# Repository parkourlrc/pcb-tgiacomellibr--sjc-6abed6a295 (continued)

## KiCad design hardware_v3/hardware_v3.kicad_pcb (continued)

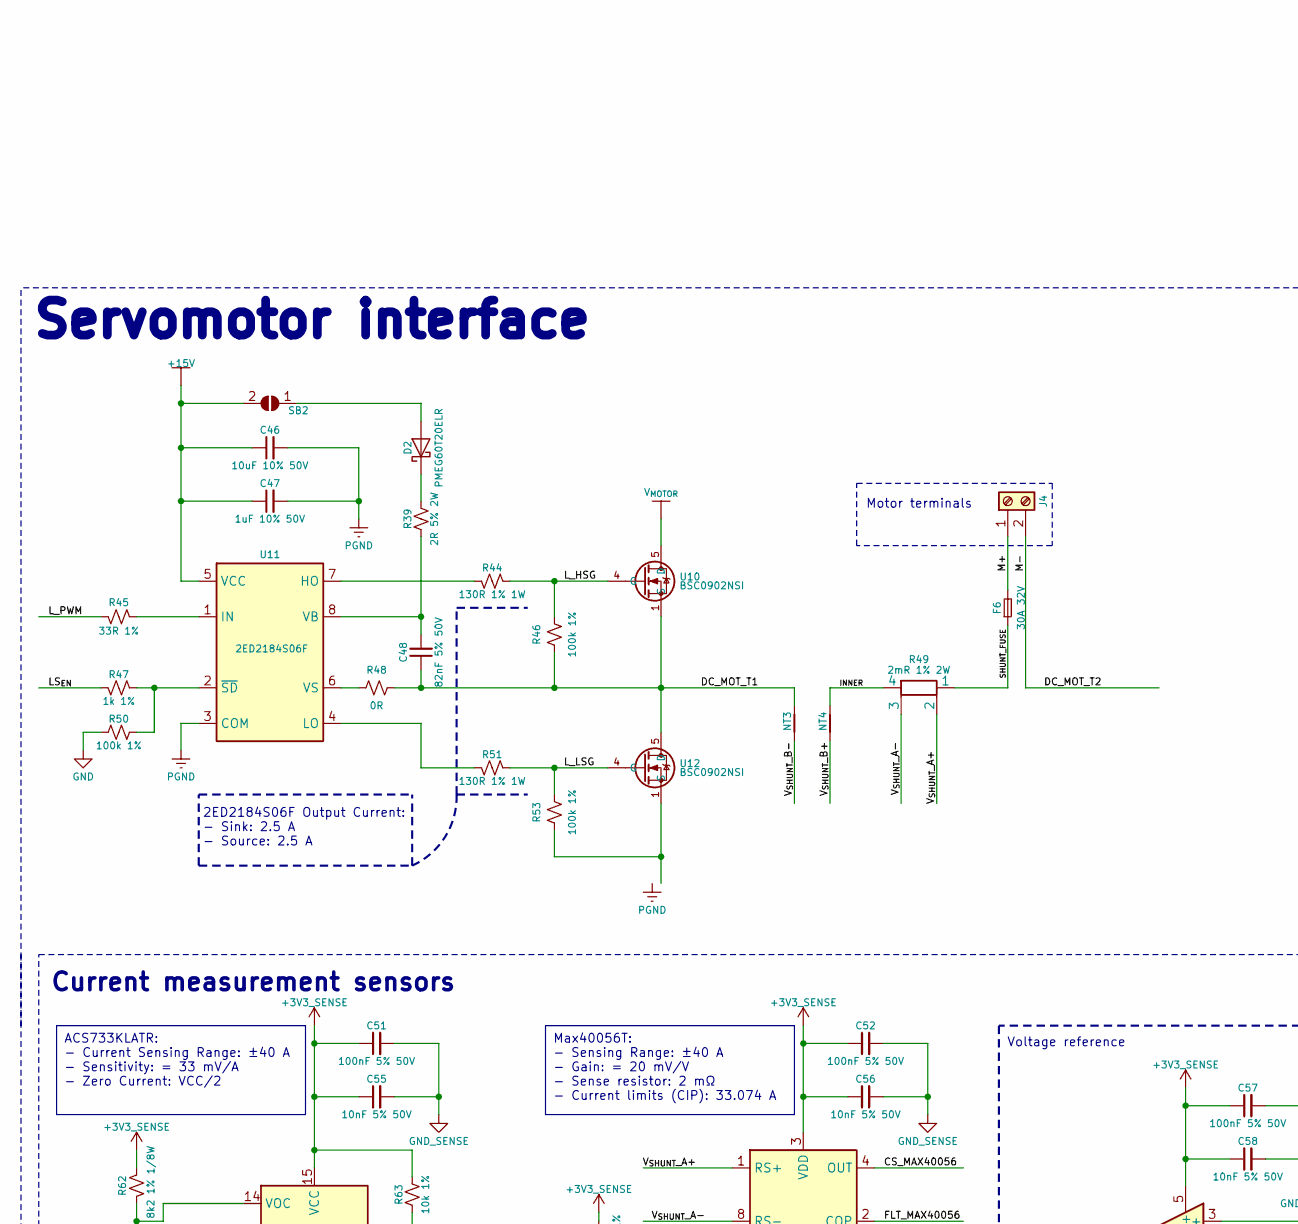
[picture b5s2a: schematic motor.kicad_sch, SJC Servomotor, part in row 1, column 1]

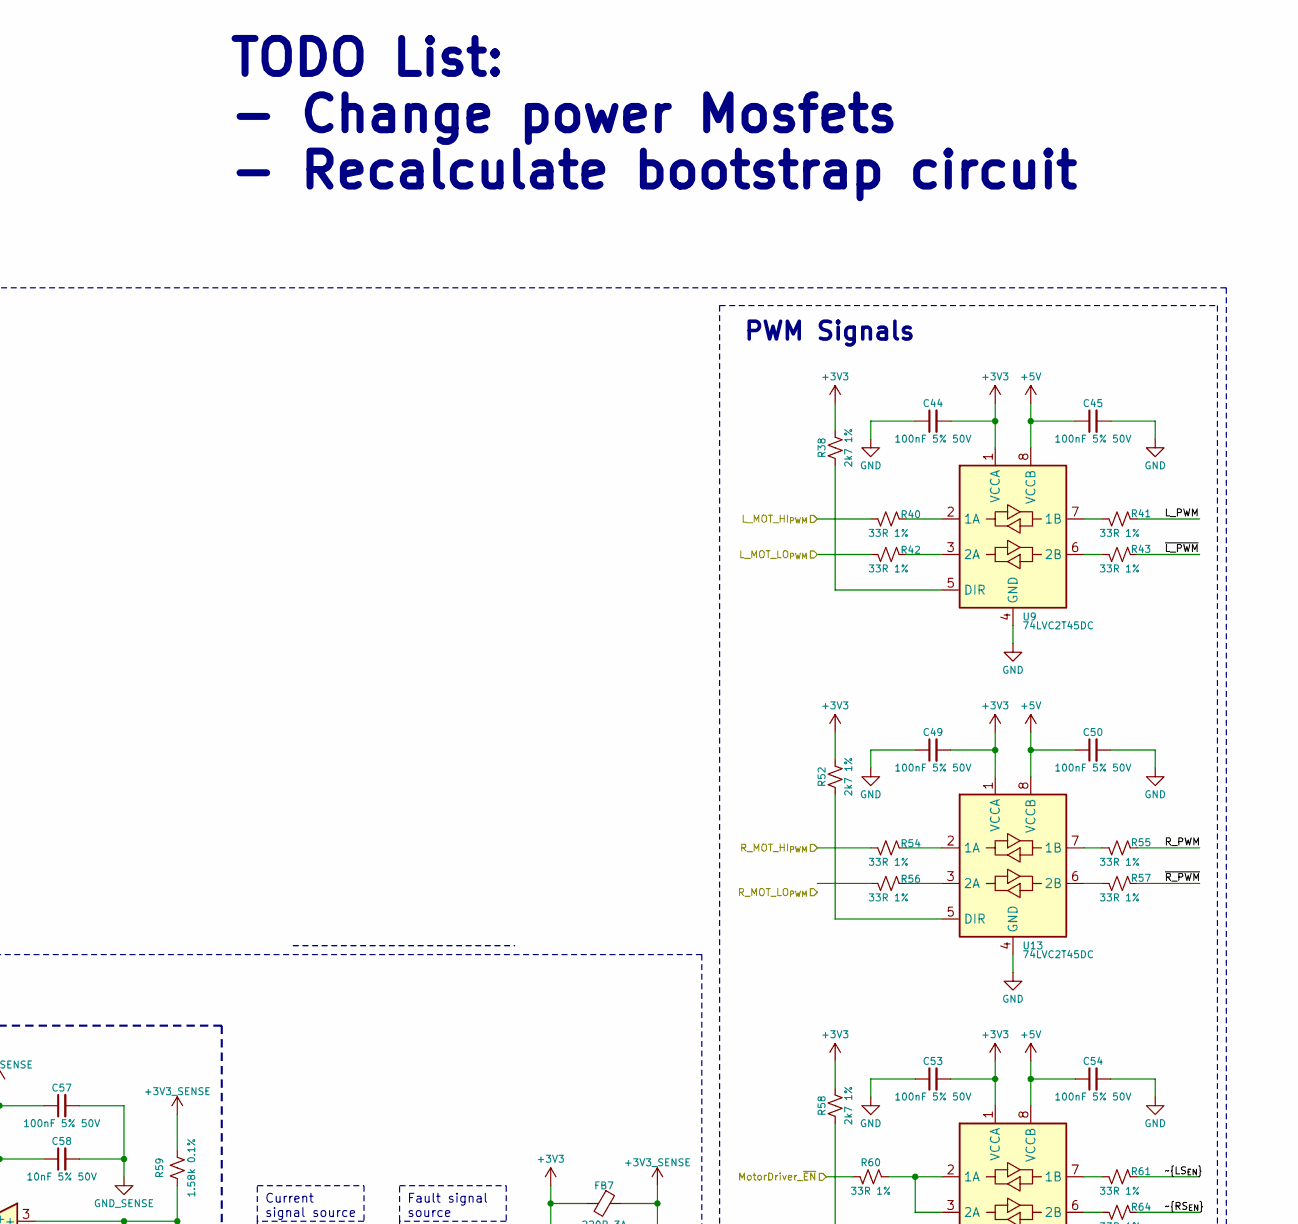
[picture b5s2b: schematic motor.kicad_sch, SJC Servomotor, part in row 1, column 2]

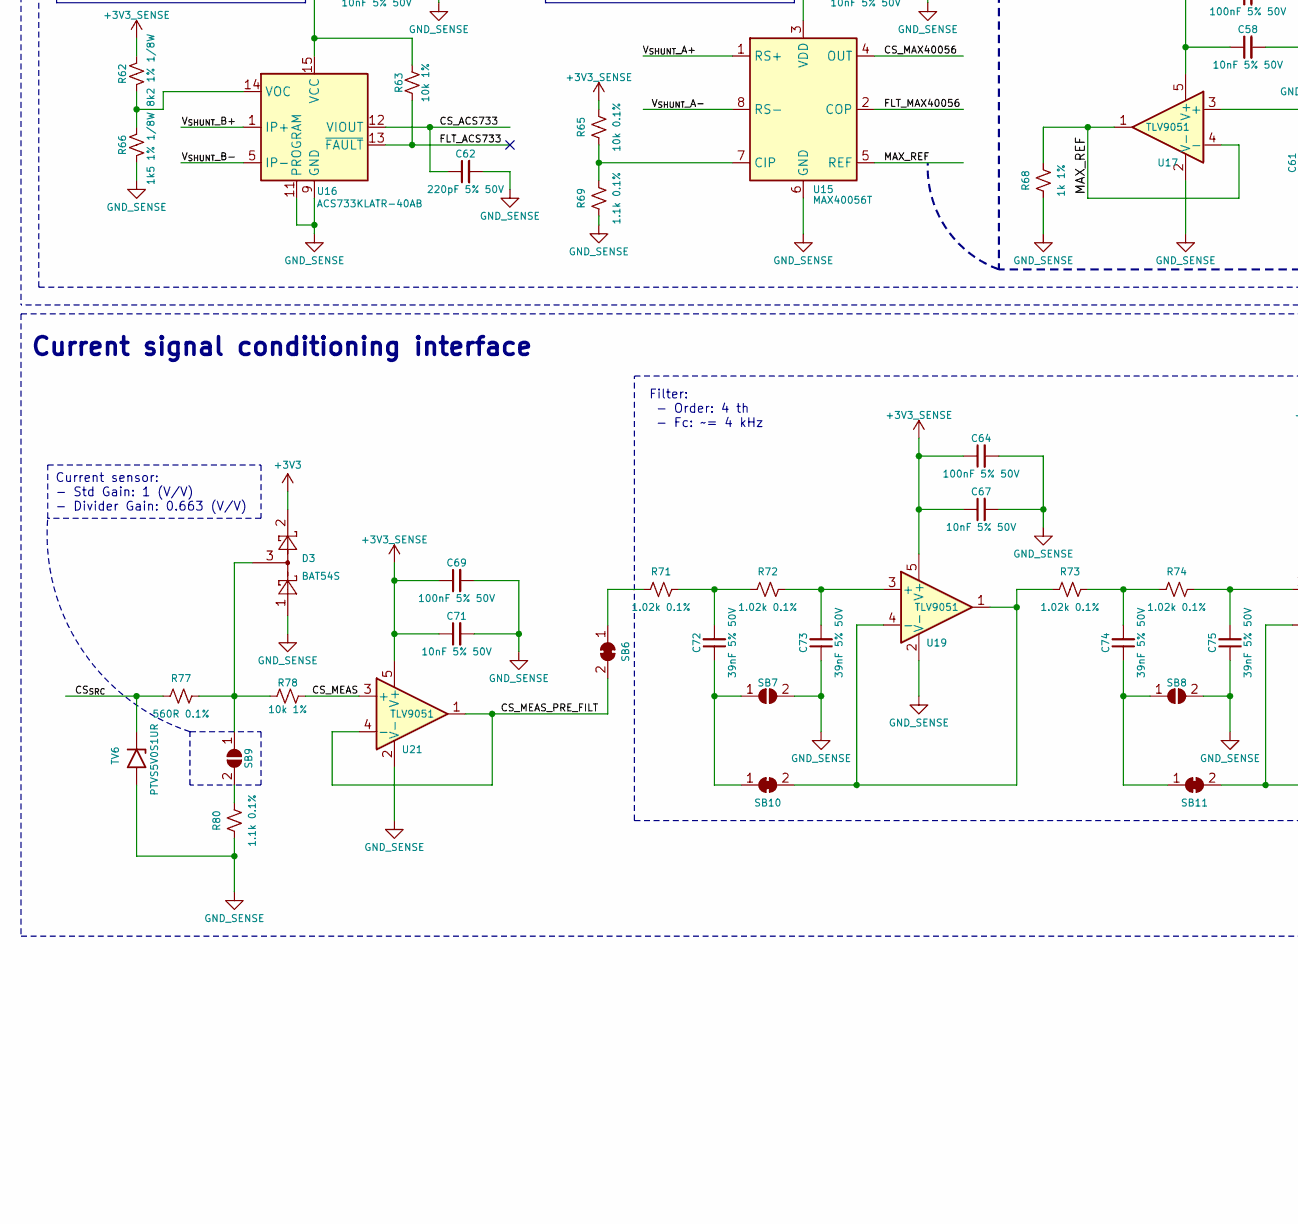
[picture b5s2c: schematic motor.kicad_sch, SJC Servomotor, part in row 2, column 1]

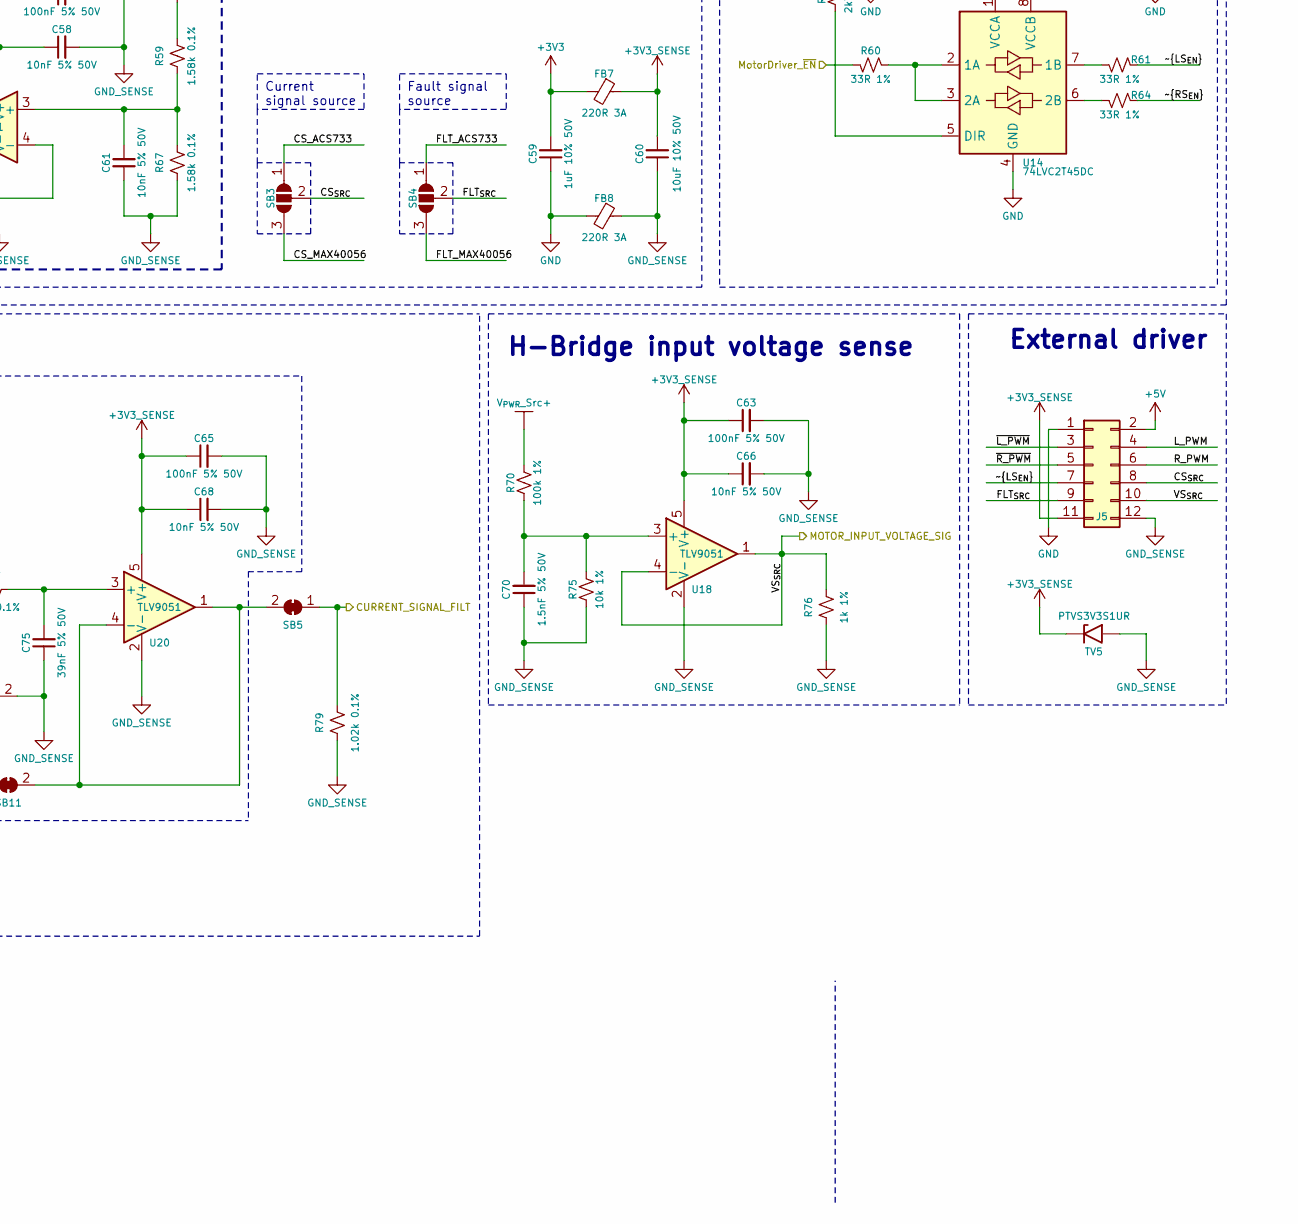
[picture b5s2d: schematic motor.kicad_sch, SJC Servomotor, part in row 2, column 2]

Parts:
C44, C45, C49, C50, C51, C52, C53, C54, C57, C63, C64, C65, C69: 100nF 5% 50V; C_0603_1608Metric; JLCPCB Part # C91183
C46, C60: 10uF 10% 50V; C_1206_3216Metric; JLCPCB Part # C13585
C47, C59: 1uF 10% 50V; C_1206_3216Metric; JLCPCB Part # C1848
C48: 82nF 5% 50V; C_0805_2012Metric_Pad1.18x1.45mm_HandSolder; JLCPCB Part # C520047
C55, C56, C58, C61, C66, C67, C68, C71: 10nF 5% 50V; C_0603_1608Metric; JLCPCB Part # C389113
C62: 220pF 5% 50V; C_0402_1005Metric_Pad0.74x0.62mm_HandSolder; JLCPCB Part # C301973
C70: 1.5nF 5% 50V; C_0603_1608Metric; JLCPCB Part # C107039
C72, C73, C74, C75: 39nF 5% 50V; C_0603_1608Metric; JLCPCB Part # C519553
D2: PMEG60T20ELR; D_SOD-123F; JLCPCB Part # C552947
D3: BAT54S; SOT-23; JLCPCB Part # C19726
F6: 30A 32V; Fuse_1206_3216Metric_Pad1.42x1.75mm_HandSolder; JLCPCB Part # C2925002
FB7, FB8: 220R 3A; L_0805_2012Metric_Pad1.05x1.20mm_HandSolder; JLCPCB Part # C76818
J4: Motor; AMASS_XT60PW-F_1x02_P7.20mm_Horizontal; JLCPCB Part # C428722
J5: Motor_Signals; PinHeader_2x06_P2.54mm_Vertical; JLCPCB Part # C225521
NT3, NT4: NetTie_2; NetTie-2_SMD_Pad2.0mm
R38, R52, R58: 2k7 1%; R_0603_1608Metric; JLCPCB Part # C114612
R39: 2R 5% 2W; R_2512_6332Metric_Pad1.40x3.35mm_HandSolder; JLCPCB Part # C91926
R40, R41, R42, R43, R45, R54, R55, R56, R57, R60, R61, R64: 33R 1%; R_0603_1608Metric; JLCPCB Part # C108661
R44, R51: 130R 1% 1W; R_2512_6332Metric_Pad1.40x3.35mm_HandSolder; JLCPCB Part # C728111
R46, R50, R53, R70: 100k 1%; R_0603_1608Metric; JLCPCB Part # C14675
R47, R68, R76: 1k 1%; R_0603_1608Metric; JLCPCB Part # C22548
R48: 0R; R_0603_1608Metric; JLCPCB Part # C103196
R49: 2mR 1% 2W; R_Shunt_2512_6332Metric_Pad1.40x3.35mm_HandSolder; JLCPCB Part # C782073
R59, R67: 1.58k 0.1%; R_0603_1608Metric; JLCPCB Part # C2441192
R62: 8k2 1% 1/8W; R_0805_2012Metric_Pad1.20x1.40mm_HandSolder; JLCPCB Part # C114545
R63, R75, R78: 10k 1%; R_0603_1608Metric; JLCPCB Part # C98220
R65: 10k 0.1%; R_0805_2012Metric_Pad1.20x1.40mm_HandSolder; JLCPCB Part # C705819
R66: 1k5 1% 1/8W; R_0805_2012Metric_Pad1.20x1.40mm_HandSolder; JLCPCB Part # C163950
R69, R80: 1.1k 0.1%; R_0603_1608Metric; JLCPCB Part # C543640
R71, R72, R73, R74, R79: 1.02k 0.1%; R_0603_1608Metric; JLCPCB Part # C705819
R77: 560R 0.1%; R_0603_1608Metric; JLCPCB Part # C351641
SB2, SB7, SB8, SB9: SolderJumper-2_P1.3mm_Open_RoundedPad1.0x1.5mm
SB3, SB4: CS_SEL; SolderJumper-3_P1.3mm_Open_RoundedPad1.0x1.5mm
SB5, SB6, SB10, SB11: SolderJumper-2_P1.3mm_Bridged2Bar_RoundedPad1.0x1.5mm
TV5: PTVS3V3S1UR; D_SOD-123; JLCPCB Part # C183521
TV6: PTVS5V0S1UR; D_SOD-123; JLCPCB Part # C478011
U9, U13, U14: 74LVC2T45DC; VSSOP-8_2.3x2mm_P0.5mm; JLCPCB Part # C730237
U10, U12: BSC0902NSI; TDSON-8-1; JLCPCB Part # C534382
U11: 2ED2184S06F; Infineon_PG-DSO-8-24_4x5mm; JLCPCB Part # C1848362
U15: MAX40056T; Texas_S-PDSO-G8_3x3mm_P0.65mm; Mouser # 700-MAX40056TAUA+
U16: ACS733KLATR-40AB; SOIC-16W_7.5x10.3mm_P1.27mm; JLCPCB Part # C459339
U17, U18, U19, U20, U21: TLV9051; SOT-23-5; JLCPCB Part # C1849429

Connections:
+3V3: C44.2, C49.2, C53.2, C59.2, D3.2, FB7.2, R38.2, R52.2, R58.2, U9.1 (VCCA), U13.1 (VCCA), U14.1 (VCCA); also elsewhere on the board
+3V3_SENSE: C51.1, C52.1, C55.1, C56.1, C57.1, C58.1, C60.2, C63.1, C64.1, C65.1, C66.1, C67.1, C68.1, C69.1, C71.1, FB7.1, J5.11, R59.2, R62.1, R63.2, R65.2, TV5.1 (K), U15.3 (VDD), U16.15 (VCC), U16.16 (VCC), U17.5 (V+), U18.5 (V+), U19.5 (V+), U20.5 (V+), U21.5 (V+)
+5V: C45.1, C50.1, C54.1, J5.2, U9.8 (VCCB), U13.8 (VCCB), U14.8 (VCCB); also elsewhere on the board
+15V: C46.1, C47.1, SB2.2 (B), U11.5 (VCC)
/Control/CURRENT_SIGNAL_FILT: R79.2, SB5.1 (A); also elsewhere on the board
/Control/L_MOT_HI_{PWM}: R40.2; also elsewhere on the board
/Control/L_MOT_LO_{PWM}: R42.2; also elsewhere on the board
/Control/MotorDriver_~EN: R60.2
/Control/R_MOT_HI_{PWM}: R54.2; also elsewhere on the board
/Motor/CS_ACS733: C62.1, SB3.1 (A), U16.12 (VIOUT)
/Motor/CS_MAX40056: SB3.3 (B), U15.4 (OUT)
/Motor/CS_MEAS: R78.2, U21.3 (+)
/Motor/CS_MEAS_PRE_FILT: SB6.2 (B), U21.1, U21.4 (-)
/Motor/CS_{SRC}: J5.8, R77.1, SB3.2 (C), TV6.1 (K)
/Motor/DC_MOT_T1: C48.1, NT3.1, R46.1, R48.2, U10.1 (S), U10.2 (S), U10.3 (S), U12.5 (D)
/Motor/DC_MOT_T2: J4.2
/Motor/FLT_ACS733: R63.1, SB4.1 (A), U16.13 (~FAULT)
/Motor/FLT_MAX40056: SB4.3 (B), U15.2 (COP)
/Motor/FLT_{SRC}: J5.9, SB4.2 (C)
/Motor/INNER: NT4.1, R49.4
/Motor/LS_{EN}: R47.2
/Motor/L_HSG: R44.1, R46.2, U10.4 (G)
/Motor/L_LSG: R51.1, R53.2, U12.4 (G)
/Motor/L_PWM: J5.4, R41.1, R45.2
/Motor/M+: F6.2, J4.1
/Motor/MAX_REF: R68.2, U15.5 (REF), U17.1, U17.4 (-)
/Motor/R_PWM: J5.6, R55.1
/Motor/SHUNT_FUSE: F6.1, R49.1
/Motor/VS_{SRC}: J5.10, R76.2, U18.1, U18.4 (-); also elsewhere on the board
/Motor/V_{SHUNT}_A+: R49.2, U15.1 (RS+)
/Motor/V_{SHUNT}_A-: R49.3, U15.8 (RS-)
/Motor/V_{SHUNT}_B+: NT4.2, U16.1 (IP+), U16.2 (IP+), U16.3 (IP+), U16.4 (IP+)
/Motor/V_{SHUNT}_B-: NT3.2, U16.5 (IP-), U16.6 (IP-), U16.7 (IP-), U16.8 (IP-)
/Motor/~LS_{EN}: J5.7, R61.1
/Motor/~L_PWM: J5.3, R43.1
/Motor/~RS_{EN}: R64.1
/Motor/~R_PWM: J5.5, R57.1
GND: C44.1, C45.2, C49.1, C50.2, C53.1, C54.2, C59.1, FB8.2, J5.1, R50.1, U9.4 (GND), U13.4 (GND), U14.4 (GND); also elsewhere on the board
GND_SENSE: C51.2, C52.2, C55.2, C56.2, C57.2, C58.2, C60.1, C61.1, C62.2, C63.2, C64.2, C65.2, C66.2, C67.2, C68.2, C69.2, C70.1, C71.2, C73.1, C75.1, D3.1, FB8.1, J5.12, R66.2, R67.1, R68.1, R69.1, R75.1, R76.1, R79.1, R80.1, SB7.2 (B), SB8.2 (B), TV5.2 (A), TV6.2 (A), U15.6 (GND), U16.9 (GND), U16.10 (GND), U16.11 (PROGRAM), U17.2 (V-), U18.2 (V-), U19.2 (V-), U20.2 (V-), U21.2 (V-)
unnamed: C72.2, R71.2, R72.1
unnamed: C74.2, R73.2, R74.1
unnamed: D2.2 (A), SB2.1 (A)
unnamed: D2.1 (K), R39.2
unnamed: R53.1, U12.1 (S), U12.2 (S), U12.3 (S)
unnamed: R71.1, SB6.1 (A)
unnamed: D3.3, R77.2, R78.1, SB9.1 (A)
unnamed: R80.2, SB9.2 (B)
unnamed: C72.1, SB7.1 (A), SB10.1 (A)
unnamed: R73.1, SB10.2 (B), U19.1, U19.4 (-)
unnamed: C74.1, SB8.1 (A), SB11.1 (A)
unnamed: SB5.2 (B), SB11.2 (B), U20.1, U20.4 (-)
unnamed: R40.1, U9.2 (1A)
unnamed: R41.2, U9.7 (1B)
unnamed: R42.1, U9.3 (2A)
unnamed: R43.2, U9.6 (2B)
unnamed: R38.1, U9.5 (DIR)
unnamed: R44.2, U11.7 (HO)
unnamed: R45.1, U11.1 (IN)
unnamed: R51.2, U11.4 (LO)
unnamed: C48.2, R39.1, U11.8 (VB)
unnamed: R48.1, U11.6 (VS)
unnamed: R47.1, R50.2, U11.2 (~SD)
unnamed: R54.1, U13.2 (1A)
unnamed: R55.2, U13.7 (1B)
unnamed: R56.1, U13.3 (2A)
unnamed: R57.2, U13.6 (2B)
unnamed: R52.1, U13.5 (DIR)
unnamed: R60.1, U14.2 (1A), U14.3 (2A)
unnamed: R61.2, U14.7 (1B)
unnamed: R64.2, U14.6 (2B)
unnamed: R58.1, U14.5 (DIR)
unnamed: R65.1, R69.2, U15.7 (CIP)
unnamed: R62.2, R66.1, U16.14 (VOC)
unnamed: C61.2, R59.1, R67.2, U17.3 (+)
unnamed: C70.2, R70.1, R75.2, U18.3 (+)
unnamed: C73.2, R72.2, U19.3 (+)
unnamed: C75.2, R74.2, U20.3 (+)
PGND: C46.2, C47.2, U11.3 (COM); also elsewhere on the board
V_{MOTOR}: U10.5 (D)
V_{PWR}_Src+: R70.2; also elsewhere on the board

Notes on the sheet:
Current sensor: - Std Gain: 1 (V/V) - Divider Gain: 0.663 (V/V)
ACS733KLATR: - Current Sensing Range: ±40 A - Sensitivity: = 33 mV/A - Zero Current: VCC/2
Fault signal source
Max40056T: - Sensing Range: ±40 A - Gain: = 20 mV/V - Sense resistor: 2 mΩ - Current limits (CIP): 33.074 A
Current signal source
Current signal conditioning interface
H-Bridge input voltage sense
Voltage reference
External driver
Filter: - Order: 4 th - Fc: ~= 4 kHz
2ED2184S06F Output Current: - Sink: 2.5 A - Source: 2.5 A
Servomotor interface
Motor terminals
PWM Signals
Current measurement sensors
TODO List: - Change power Mosfets - Recalculate bootstrap circuit

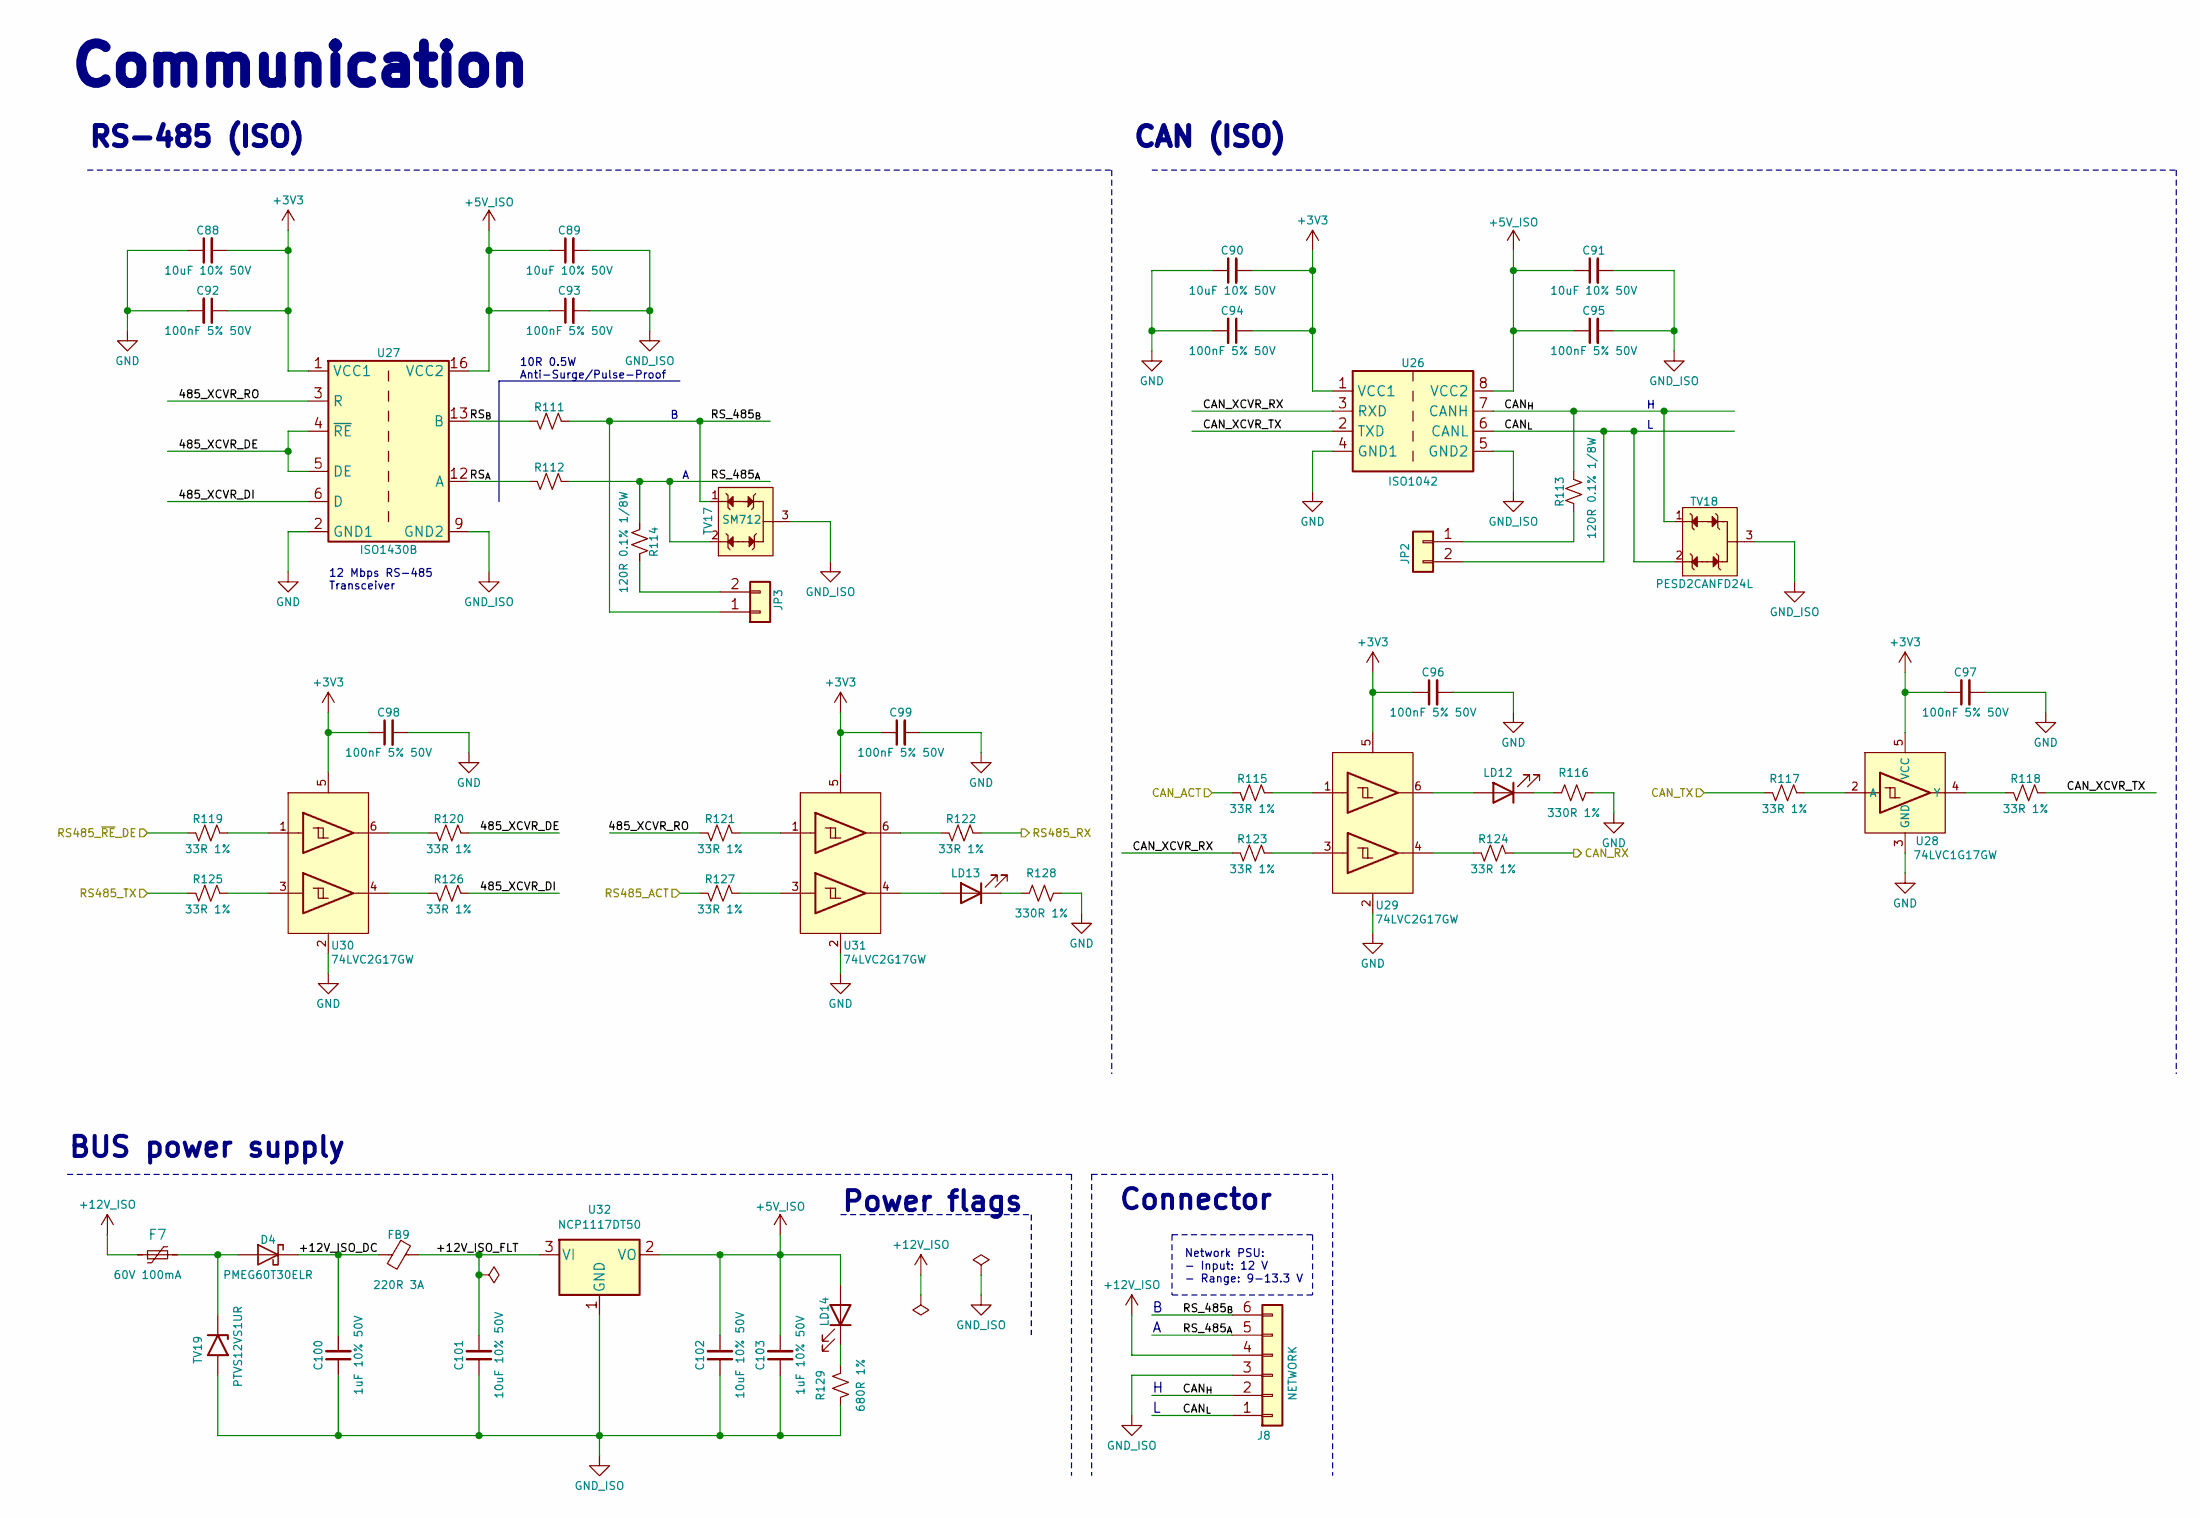
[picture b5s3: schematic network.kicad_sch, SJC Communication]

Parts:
C88, C89, C90, C91, C101, C102: 10uF 10% 50V; C_1206_3216Metric; JLCPCB Part # C13585
C92, C93, C94, C95, C96, C97, C98, C99: 100nF 5% 50V; C_0603_1608Metric; JLCPCB Part # C91183
C100, C103: 1uF 10% 50V; C_1206_3216Metric; JLCPCB Part # C1848
D4: PMEG60T30ELR; D_SOD-123F; JLCPCB Part # C2938304
F7: 60V 100mA; Fuse_1206_3216Metric; JLCPCB Part # C2153714
FB9: 220R 3A; L_0805_2012Metric_Pad1.05x1.20mm_HandSolder; JLCPCB Part # C76818
J8: NETWORK; TerminalBlock_Phoenix_MKDS-3-6-5.08_1x06_P5.08mm_Horizontal; JLCPCB Part # C2915642
JP2, JP3: RS-485 TERM; PinHeader_1x02_P2.54mm_Vertical; JLCPCB Part # C225477
LD12, LD13, LD14: 1.8V @ 5mA; LED_0603_1608Metric_Pad1.05x0.95mm_HandSolder; JLCPCB Part # C165982
R111, R112: 10R 5% 1/2W; R_0805_2012Metric_Pad1.20x1.40mm_HandSolder; JLCPCB Part # C966152
R113, R114: 120R 0.1% 1/8W; R_0805_2012Metric_Pad1.20x1.40mm_HandSolder; JLCPCB Part # C2828708
R115, R117, R118, R119, R120, R121, R122, R123, R124, R125, R126, R127: 33R 1%; R_0603_1608Metric; JLCPCB Part # C108661
R116, R128: 330R 1%; R_0603_1608Metric; JLCPCB Part # C144102
R129: 680R 1%; R_0603_1608Metric; JLCPCB Part # C966615
TV17: SM712; SOT-23-3; JLCPCB Part # C293966
TV18: PESD2CANFD24L; SOT-23W_Handsoldering; LCSC Part # C3711787
TV19: PTVS12VS1UR; D_SOD-123; JLCPCB Part # C456115
U26: ISO1042; SOIC-8_7.5x5.85mm_P1.27mm; JLCPCB Part # C2671714
U27: ISO1430B; SOIC-16W_7.5x10.3mm_P1.27mm; JLCPCB Part # C2869747
U28: 74LVC1G17GW; SOT-353_SC-70-5_Handsoldering; JLCPCB Part # C426705
U29, U30, U31: 74LVC2G17GW; SOT-363_SC-70-6; JLCPCB Part # C80500
U32: NCP1117DT50; TO-252-2; JLCPCB Part # C152470

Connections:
+3V3: C88.2, C90.2, C92.1, C94.1, C96.1, C97.1, C98.1, C99.1, U26.1 (VCC1), U27.1 (VCC1), U28.5 (VCC), U29.5 (VCC), U30.5 (VCC), U31.5 (VCC); also elsewhere on the board
+5V_ISO: C89.1, C91.1, C93.1, C95.1, C102.2, C103.2, LD14.2 (A), U26.8 (VCC2), U27.16 (VCC2), U32.2 (VO)
+12V_ISO: F7.1, J8.4
/Control/CAN_RX: R124.1
/Control/CAN_TX: R117.2
/Control/COM_485_RX: R122.1; also elsewhere on the board
/Control/COM_485_TX: R125.2; also elsewhere on the board
/Control/COM_485_~RE_DE: R119.2; also elsewhere on the board
/Network/485_XCVR_DE: R120.1, U27.4 (~RE), U27.5 (DE)
/Network/485_XCVR_DI: R126.1, U27.6 (D)
/Network/485_XCVR_RO: R121.2, U27.3 (R)
/Network/+12V_ISO_DC: C100.2, D4.1 (K), FB9.2
/Network/+12V_ISO_FLT: C101.2, FB9.1, U32.3 (VI)
/Network/CAN_ACT: R115.2
/Network/CAN_XCVR_RX: R123.2, U26.3 (RXD)
/Network/CAN_XCVR_TX: R118.1, U26.2 (TXD)
/Network/CAN_{H}: J8.2, R113.1, TV18.1 (K1), U26.7 (CANH)
/Network/CAN_{L}: J8.1, JP2.2, TV18.2 (K2), U26.6 (CANL)
/Network/RS485_ACT: R127.2
/Network/RS_485_{A}: J8.5, R112.1, R114.1, TV17.2
/Network/RS_485_{B}: J8.6, JP3.1, R111.1, TV17.1
/Network/RS_{A}: R112.2, U27.12 (A)
/Network/RS_{B}: R111.2, U27.13 (B)
GND: C88.1, C90.1, C92.2, C94.2, C96.2, C97.2, C98.2, C99.2, R116.2, R128.2, U26.4 (GND1), U27.2 (GND1), U27.8 (GND1), U28.3 (GND), U29.2 (GND), U30.2 (GND), U31.2 (GND); also elsewhere on the board
GND_ISO: C89.2, C91.2, C93.2, C95.2, C100.1, C101.1, C102.1, C103.1, J8.3, R129.2, TV17.3, TV18.3 (CC), TV19.2 (A), U26.5 (GND2), U27.9 (GND2), U27.15 (GND2), U32.1 (GND)
unnamed: D4.2 (A), F7.2, TV19.1 (K)
unnamed: JP2.1, R113.2
unnamed: JP3.2, R114.2
unnamed: LD12.2 (A), U29.6 (1Y)
unnamed: LD12.1 (K), R116.1
unnamed: LD13.2 (A), U31.4 (2Y)
unnamed: LD13.1 (K), R128.1
unnamed: LD14.1 (K), R129.1
unnamed: R117.1, U28.2 (A)
unnamed: R118.2, U28.4 (Y)
unnamed: R115.1, U29.1 (1A)
unnamed: R123.1, U29.3 (2A)
unnamed: R124.2, U29.4 (2Y)
unnamed: R119.1, U30.1 (1A)
unnamed: R120.2, U30.6 (1Y)
unnamed: R125.1, U30.3 (2A)
unnamed: R126.2, U30.4 (2Y)
unnamed: R121.1, U31.1 (1A)
unnamed: R122.2, U31.6 (1Y)
unnamed: R127.1, U31.3 (2A)

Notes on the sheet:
RS-485 (ISO)
10R 0.5W Anti-Surge/Pulse-Proof
Power flags
CAN (ISO)
12 Mbps RS-485 Transceiver
BUS power supply
Connector
Communication
Network PSU: - Input: 12 V - Range: 9-13.3 V

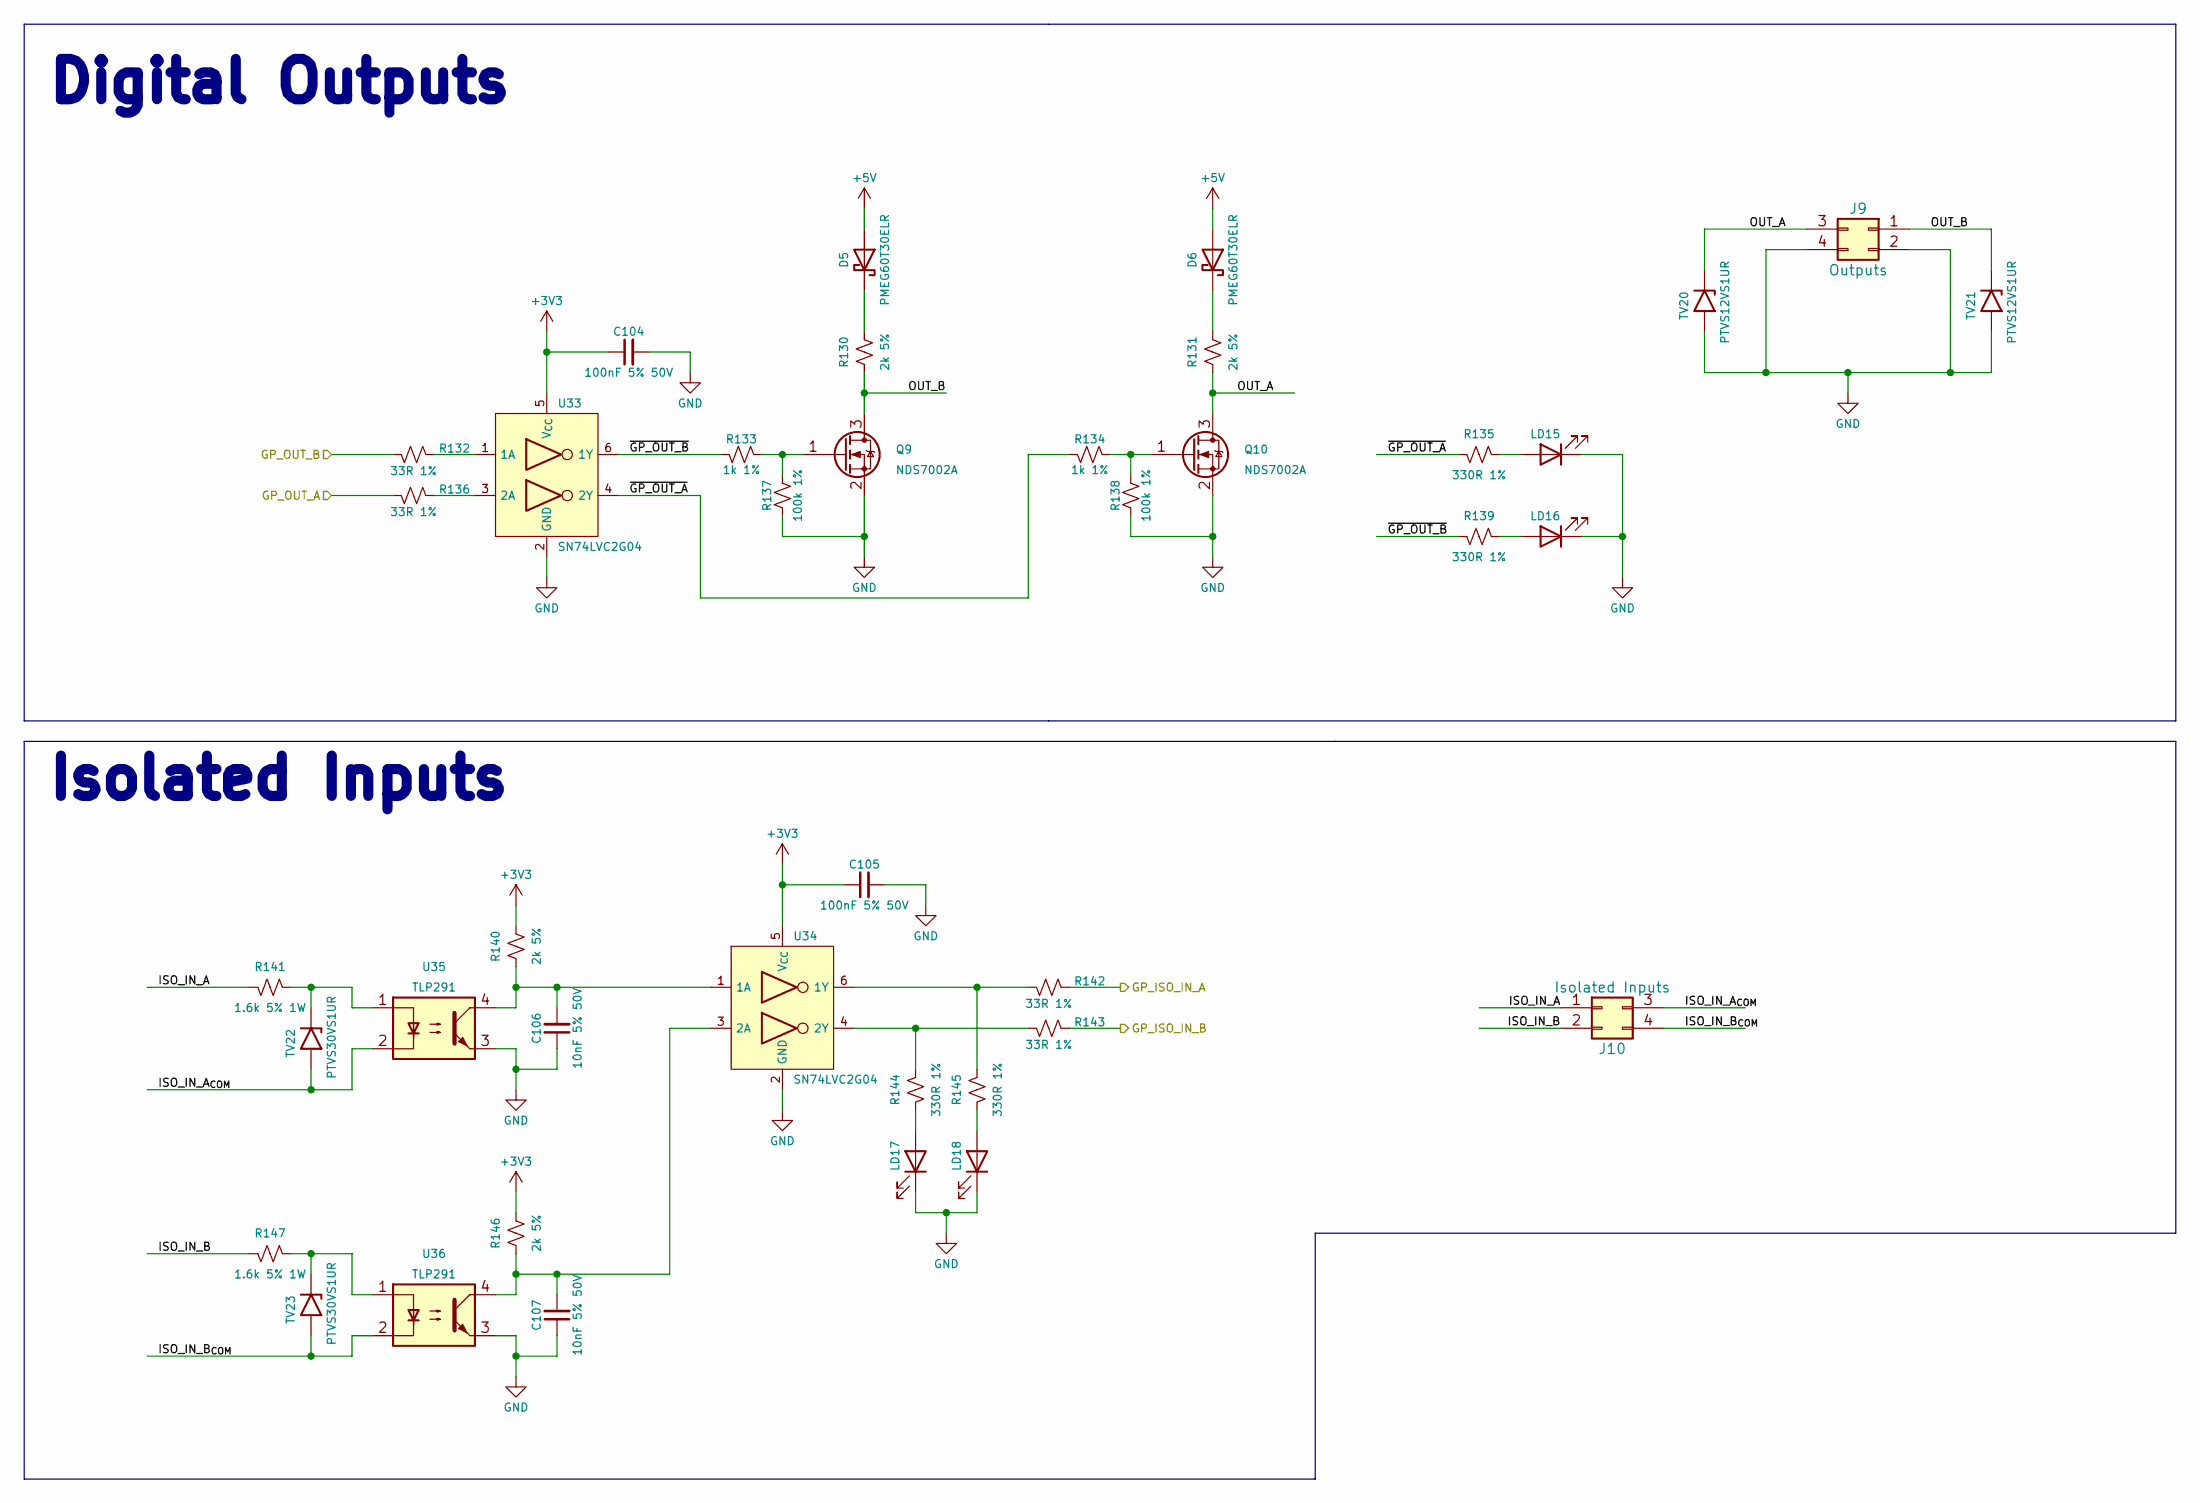
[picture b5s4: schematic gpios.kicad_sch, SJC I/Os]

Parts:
C104, C105: 100nF 5% 50V; C_0603_1608Metric; JLCPCB Part # C91183
C106, C107: 10nF 5% 50V; C_0603_1608Metric; JLCPCB Part # C389113
D5, D6: PMEG60T30ELR; D_SOD-123F; JLCPCB Part # C2938304
J9: Outputs; Molex_Micro-Fit_3.0_43045-0412_2x02_P3.00mm_Vertical
J10: Isolated Inputs; Molex_Micro-Fit_3.0_43045-0412_2x02_P3.00mm_Vertical
LD15, LD16, LD17, LD18: 1.8V @ 5mA; LED_0603_1608Metric_Pad1.05x0.95mm_HandSolder; JLCPCB Part # C165982
Q9, Q10: NDS7002A; SOT-23; JLCPCB Part # C74715
R130, R131, R140, R146: 2k 5%; R_0603_1608Metric; JLCPCB Part # C103396
R132, R136, R142, R143: 33R 1%; R_0603_1608Metric; JLCPCB Part # C108661
R133, R134: 1k 1%; R_0603_1608Metric; JLCPCB Part # C22548
R135, R139, R144, R145: 330R 1%; R_0603_1608Metric; JLCPCB Part # C144102
R137, R138: 100k 1%; R_0603_1608Metric; JLCPCB Part # C14675
R141, R147: 1.6k 5% 1W; R_2512_6332Metric_Pad1.40x3.35mm_HandSolder; JLCPCB Part # C453392
TV20, TV21: PTVS12VS1UR; D_SOD-123; JLCPCB Part # C456115
TV22, TV23: PTVS30VS1UR; D_SOD-123; JLCPCB Part # C553410
U33, U34: SN74LVC2G04; SOT-23-6_Handsoldering; JLCPCB Part # C10428
U35, U36: TLP291; SOP-4_4.4x2.6mm_P1.27mm; JLCPCB Part # C55144

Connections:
+3V3: C104.1, C105.1, R140.2, R146.2, U33.5 (V_{CC}), U34.5 (V_{CC}); also elsewhere on the board
+5V: D5.2 (A), D6.2 (A); also elsewhere on the board
/Control/GP_ISO_IN_A: R142.1; also elsewhere on the board
/Control/GP_ISO_IN_B: R143.1; also elsewhere on the board
/Control/GP_OUT_A: R136.2; also elsewhere on the board
/Control/GP_OUT_B: R132.2; also elsewhere on the board
/GPIOs/ISO_IN_A: J10.1, R141.2
/GPIOs/ISO_IN_A_{COM}: J10.3, TV22.2 (A), U35.2
/GPIOs/ISO_IN_B: J10.2, R147.2
/GPIOs/ISO_IN_B_{COM}: J10.4, TV23.2 (A), U36.2
/GPIOs/OUT_A: J9.3, Q10.3 (D), R131.1, TV20.1 (K)
/GPIOs/OUT_B: J9.1, Q9.3 (D), R130.1, TV21.1 (K)
/GPIOs/~GP_OUT_A: R134.2, R135.2, U33.4 (2Y)
/GPIOs/~GP_OUT_B: R133.2, R139.2, U33.6 (1Y)
GND: C104.2, C105.2, C106.1, C107.1, J9.2, J9.4, LD15.1 (K), LD16.1 (K), LD17.1 (K), LD18.1 (K), Q9.2 (S), Q10.2 (S), R137.1, R138.1, TV20.2 (A), TV21.2 (A), U33.2 (GND), U34.2 (GND), U35.3, U36.3; also elsewhere on the board
unnamed: D5.1 (K), R130.2
unnamed: D6.1 (K), R131.2
unnamed: LD15.2 (A), R135.1
unnamed: LD16.2 (A), R139.1
unnamed: LD17.2 (A), R144.2
unnamed: LD18.2 (A), R145.2
unnamed: Q9.1 (G), R133.1, R137.2
unnamed: Q10.1 (G), R134.1, R138.2
unnamed: R141.1, TV22.1 (K), U35.1
unnamed: R147.1, TV23.1 (K), U36.1
unnamed: R132.1, U33.1 (1A)
unnamed: R136.1, U33.3 (2A)
unnamed: C106.2, R140.1, U34.1 (1A), U35.4
unnamed: R142.2, R145.1, U34.6 (1Y)
unnamed: C107.2, R146.1, U34.3 (2A), U36.4
unnamed: R143.2, R144.1, U34.4 (2Y)

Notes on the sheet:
Isolated Inputs
Digital Outputs
